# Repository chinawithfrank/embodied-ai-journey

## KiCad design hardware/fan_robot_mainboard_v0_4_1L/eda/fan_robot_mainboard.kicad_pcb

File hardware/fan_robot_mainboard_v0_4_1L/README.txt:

FanRobot V0.4 单面铜重设计试排 / 工程草案 / 禁止投板
打开 eda/fan_robot_mainboard.kicad_pro。本目录没有生产 ZIP。V0.3 制造文件没有改动。

目标：保留 60×50 mm 外形、54×44 mm 安装孔距、三节干电池、V0.3 网表与集成芯片。将贴片元件放在 F.Cu 侧，插针和 JST 插件从另一侧安装，正面焊接；保留禁布天线区域。重排了开关、阻容和测试点。原外壳的按键开窗、相机接线、底部插拔和电池线净空不能沿用未经核对的假设。J5 改面后应按新板针1核对线束，不能照旧板照片插接。

当前板：背面全板禁走线、禁铺铜、禁过孔。KiCad 工作叠层仍显示 F/B，通孔器件仍使用通孔焊盘模型；不能用默认双层导出命令投板。ESP32 中心 41 号接地焊盘保留，取消了原封装用来连到底层的散热孔，这项改变并未经过热验证。新板未达到制造条件；原理图 ERC 无误不等于 PCB 全部连通。

检查依据：checks/drc.rpt 为完整原生 DRC（含与原理图的一致性）；checks/status.json 为本版几何/开路统计。评审时以这两个文件为准。
继续设计：按功能分区重新排列相机并口、USB差分对、电源输入到两路开关转换器、电机驱动到限流电阻；逐项处理跨线。若采用0Ω跨接，需进入原理图、BOM与贴装文件；高电流与反馈不能随意通过细跳线绕行。若放大板框，需同步核对机壳。投板前必须清除未连接/短路、检查实际单铜面焊盘及钻孔、复核地回路和散热，并用新板生成专属 Gerber/BOM/CPL。不要从 V0.3 删掉底铜来下单。

工程维护：layout.py 用 KiCad 10 Python 从邻目录 V0.3 重新生成布局（会覆盖 PCB），可带临时 DSN 输出路径；使用 Freerouting 2.1.0 做禁止背面和过孔的试布；finish.py 输入选定的 SES，导入并重新填铜。用 kicad-cli pcb drc --all-track-errors --schematic-parity 输出最新报告，再运行 check-layout.py。在打开现成草案时不需要运行这些脚本。

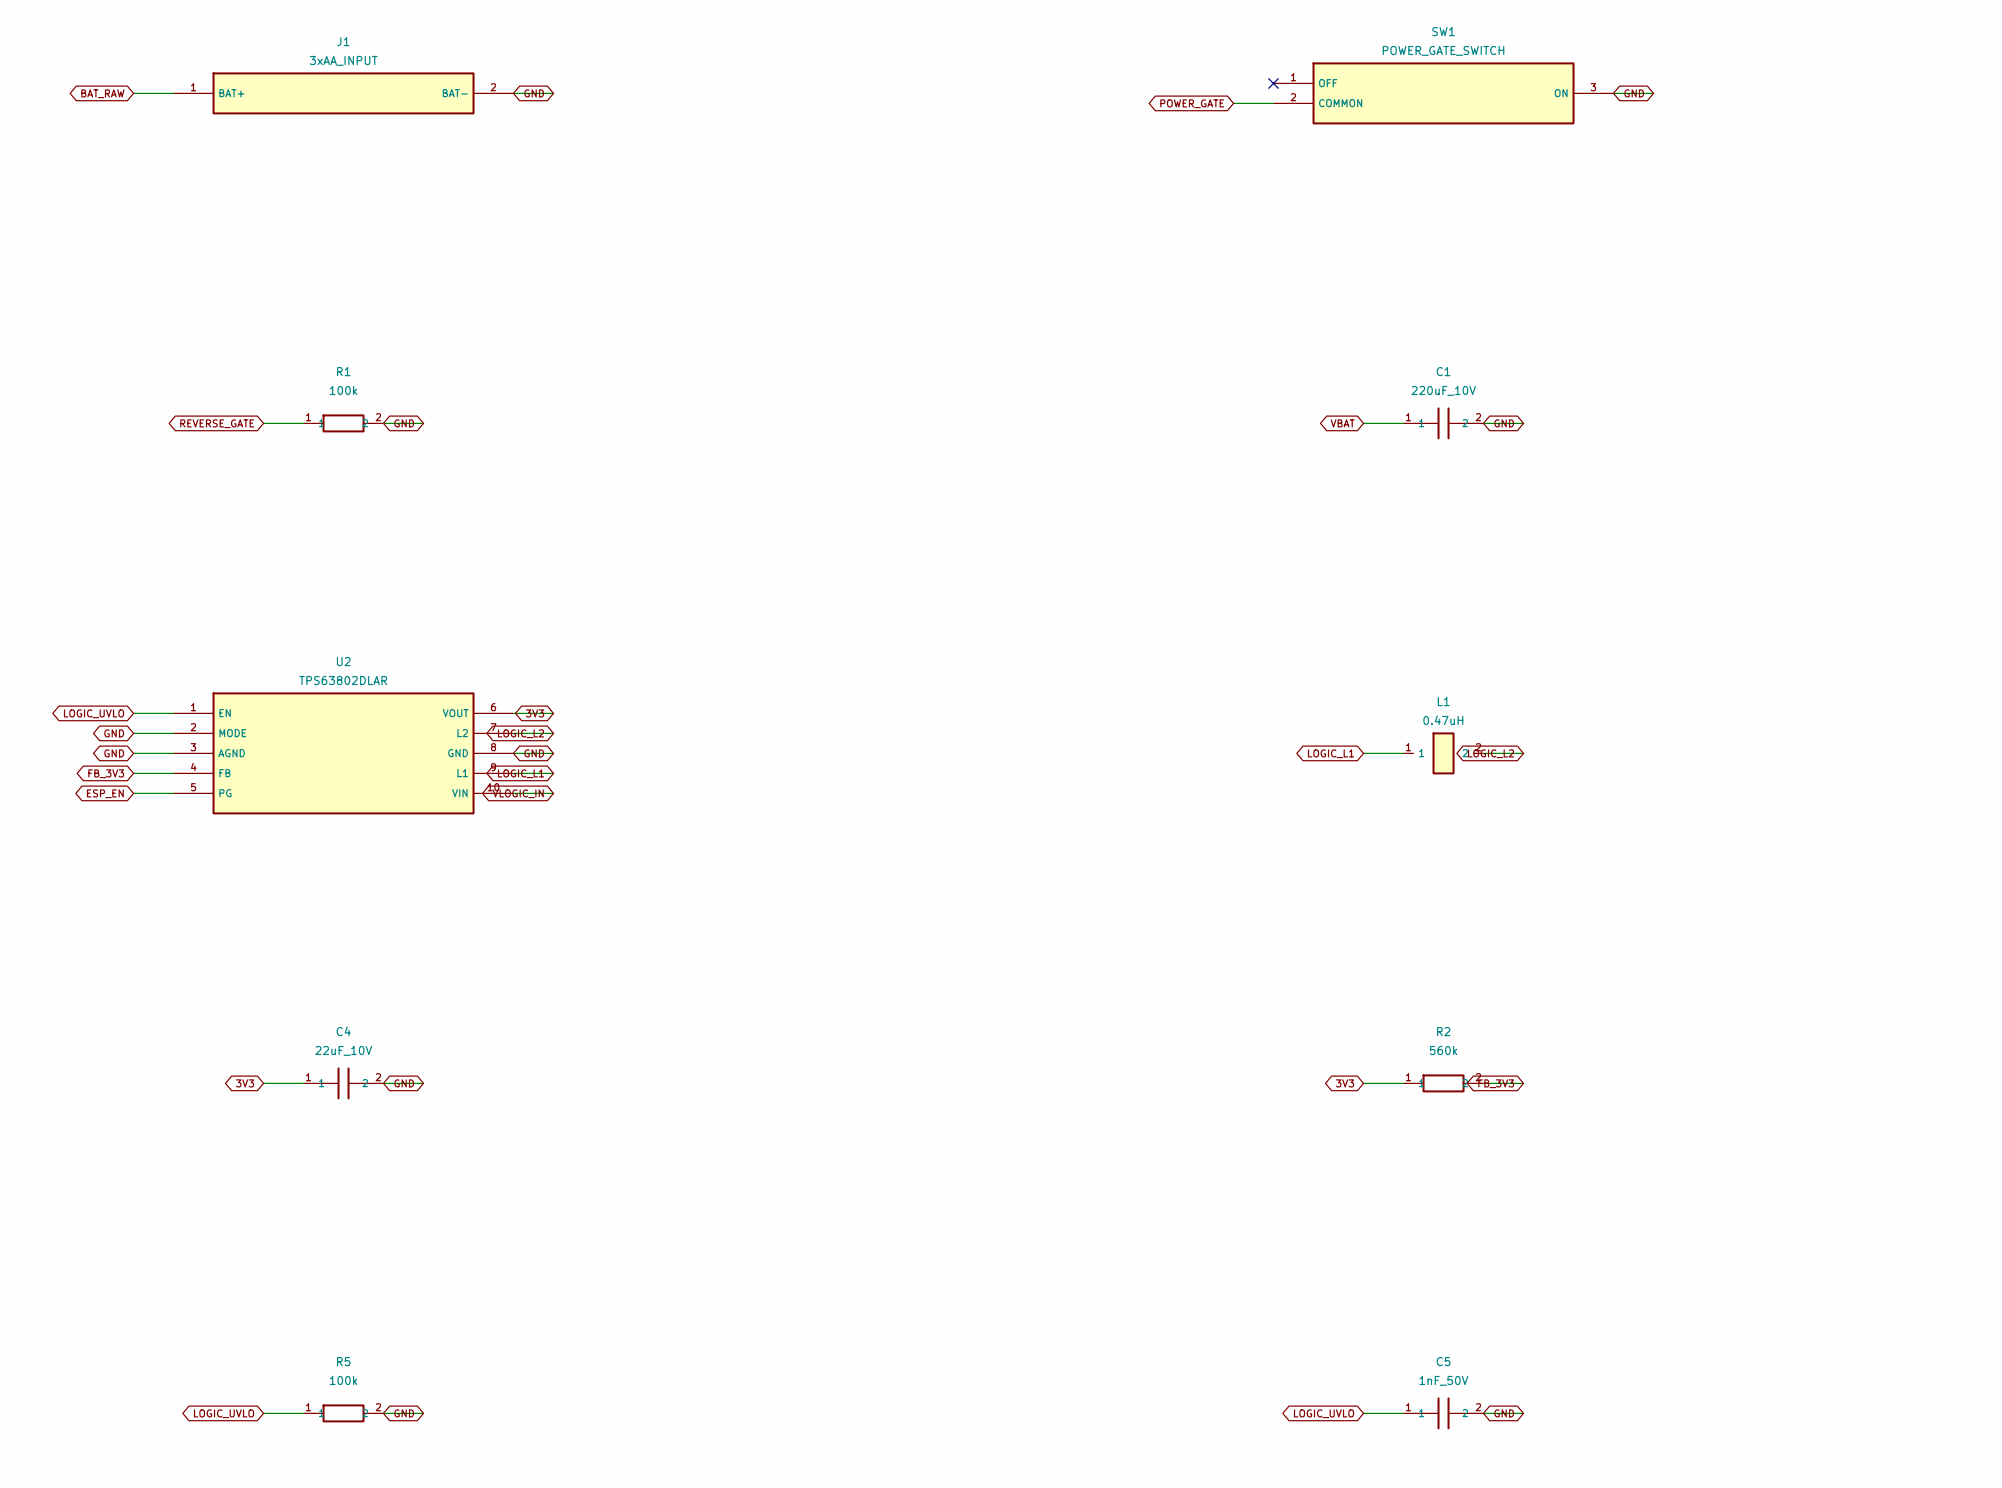
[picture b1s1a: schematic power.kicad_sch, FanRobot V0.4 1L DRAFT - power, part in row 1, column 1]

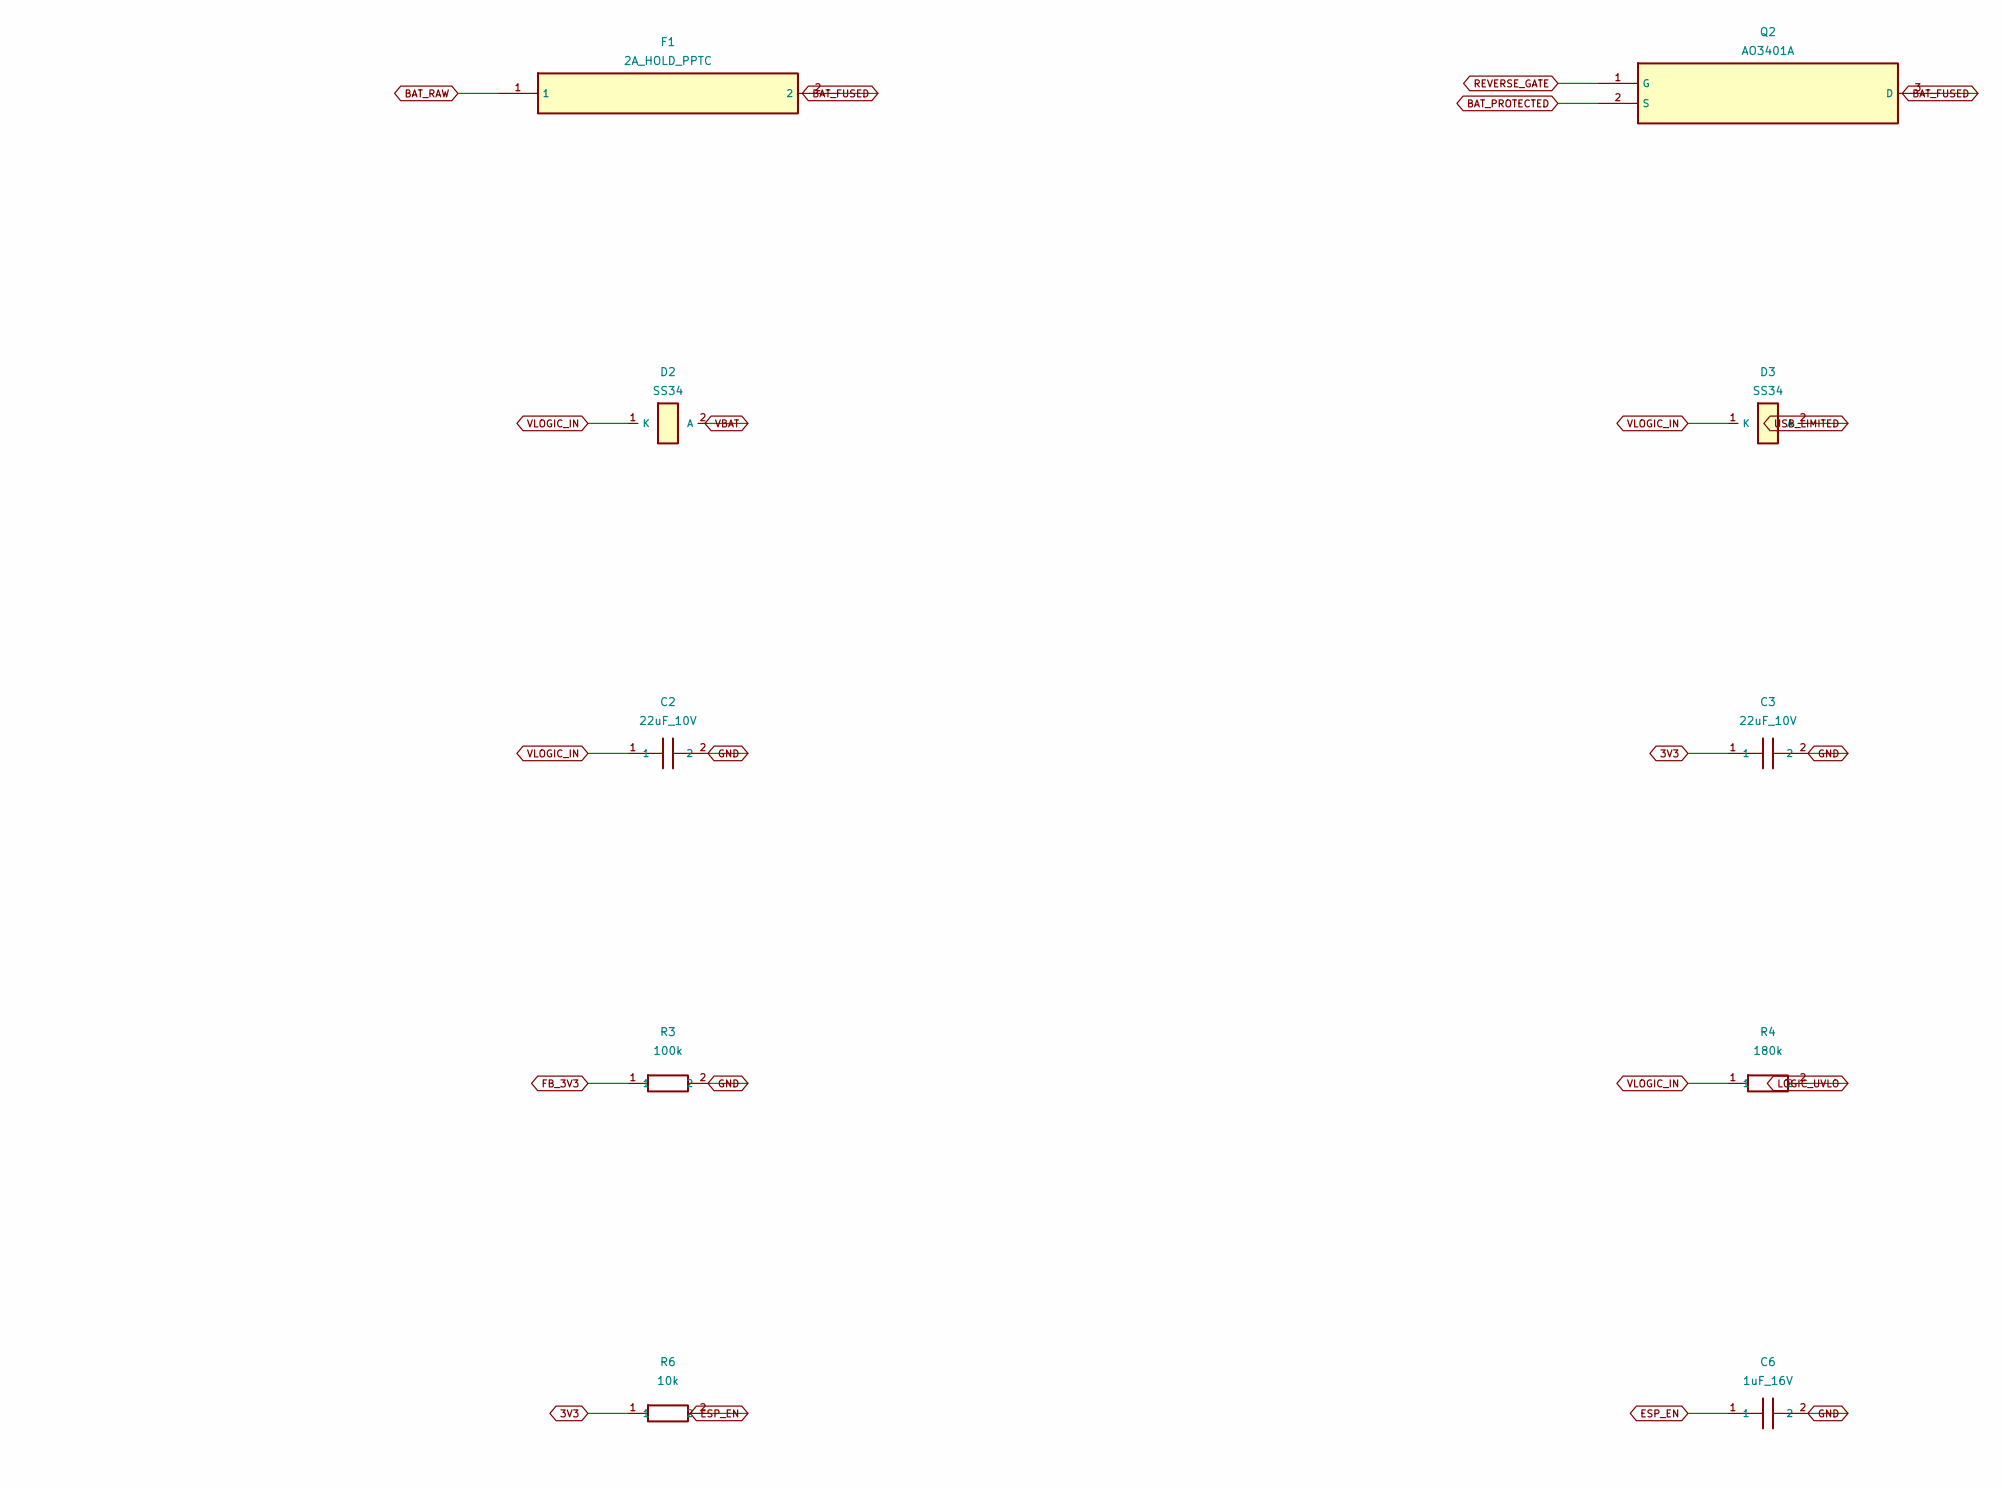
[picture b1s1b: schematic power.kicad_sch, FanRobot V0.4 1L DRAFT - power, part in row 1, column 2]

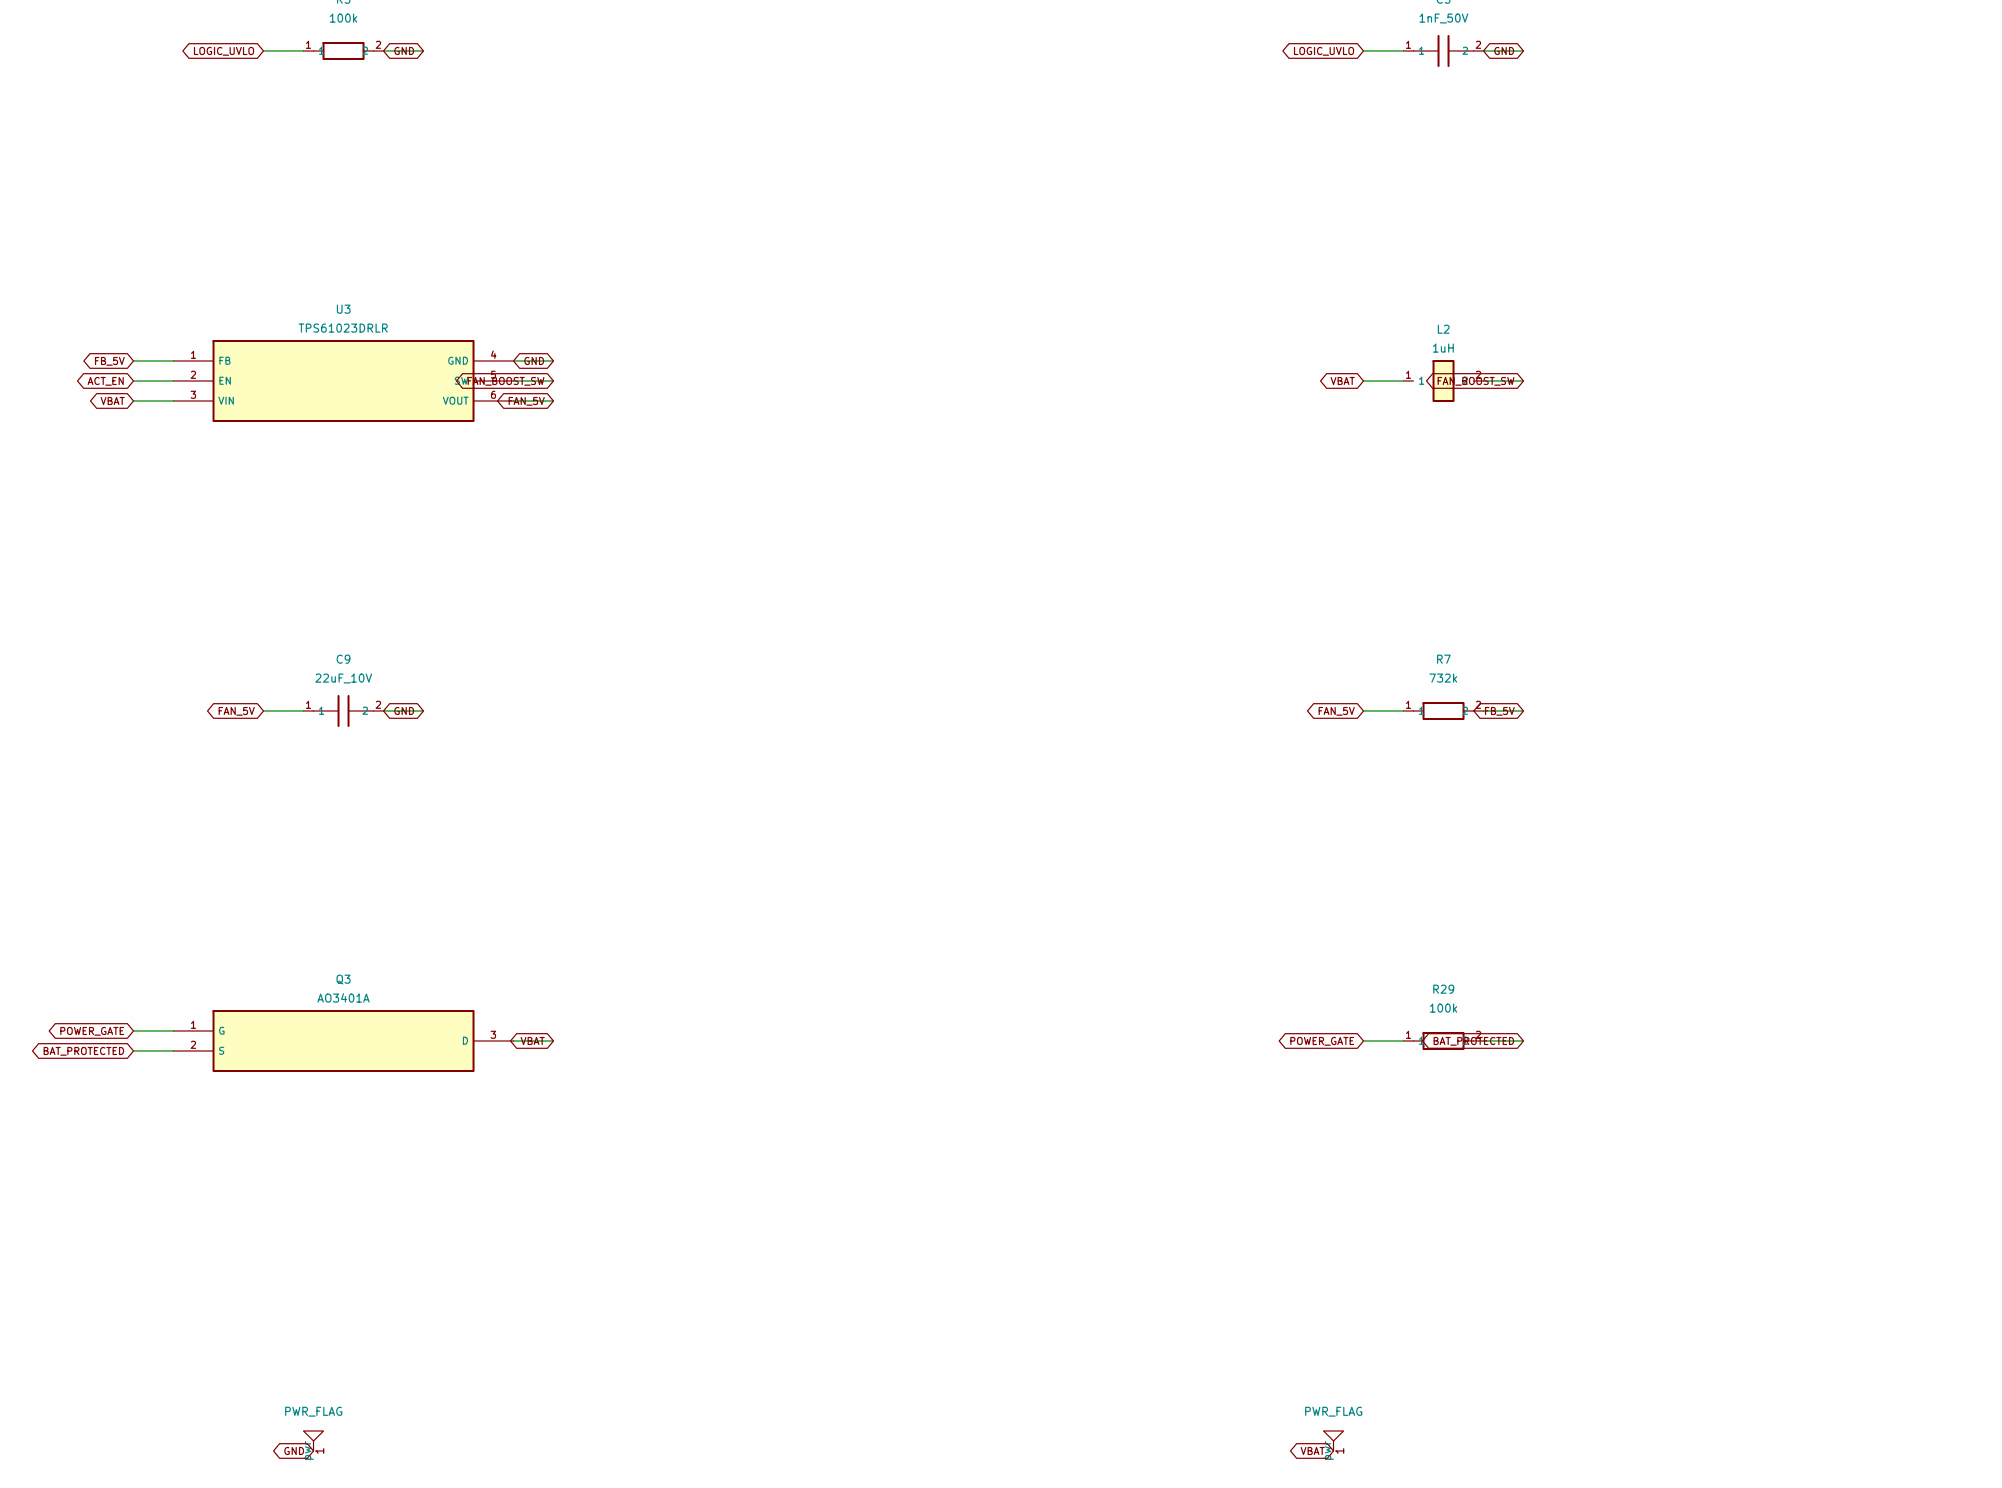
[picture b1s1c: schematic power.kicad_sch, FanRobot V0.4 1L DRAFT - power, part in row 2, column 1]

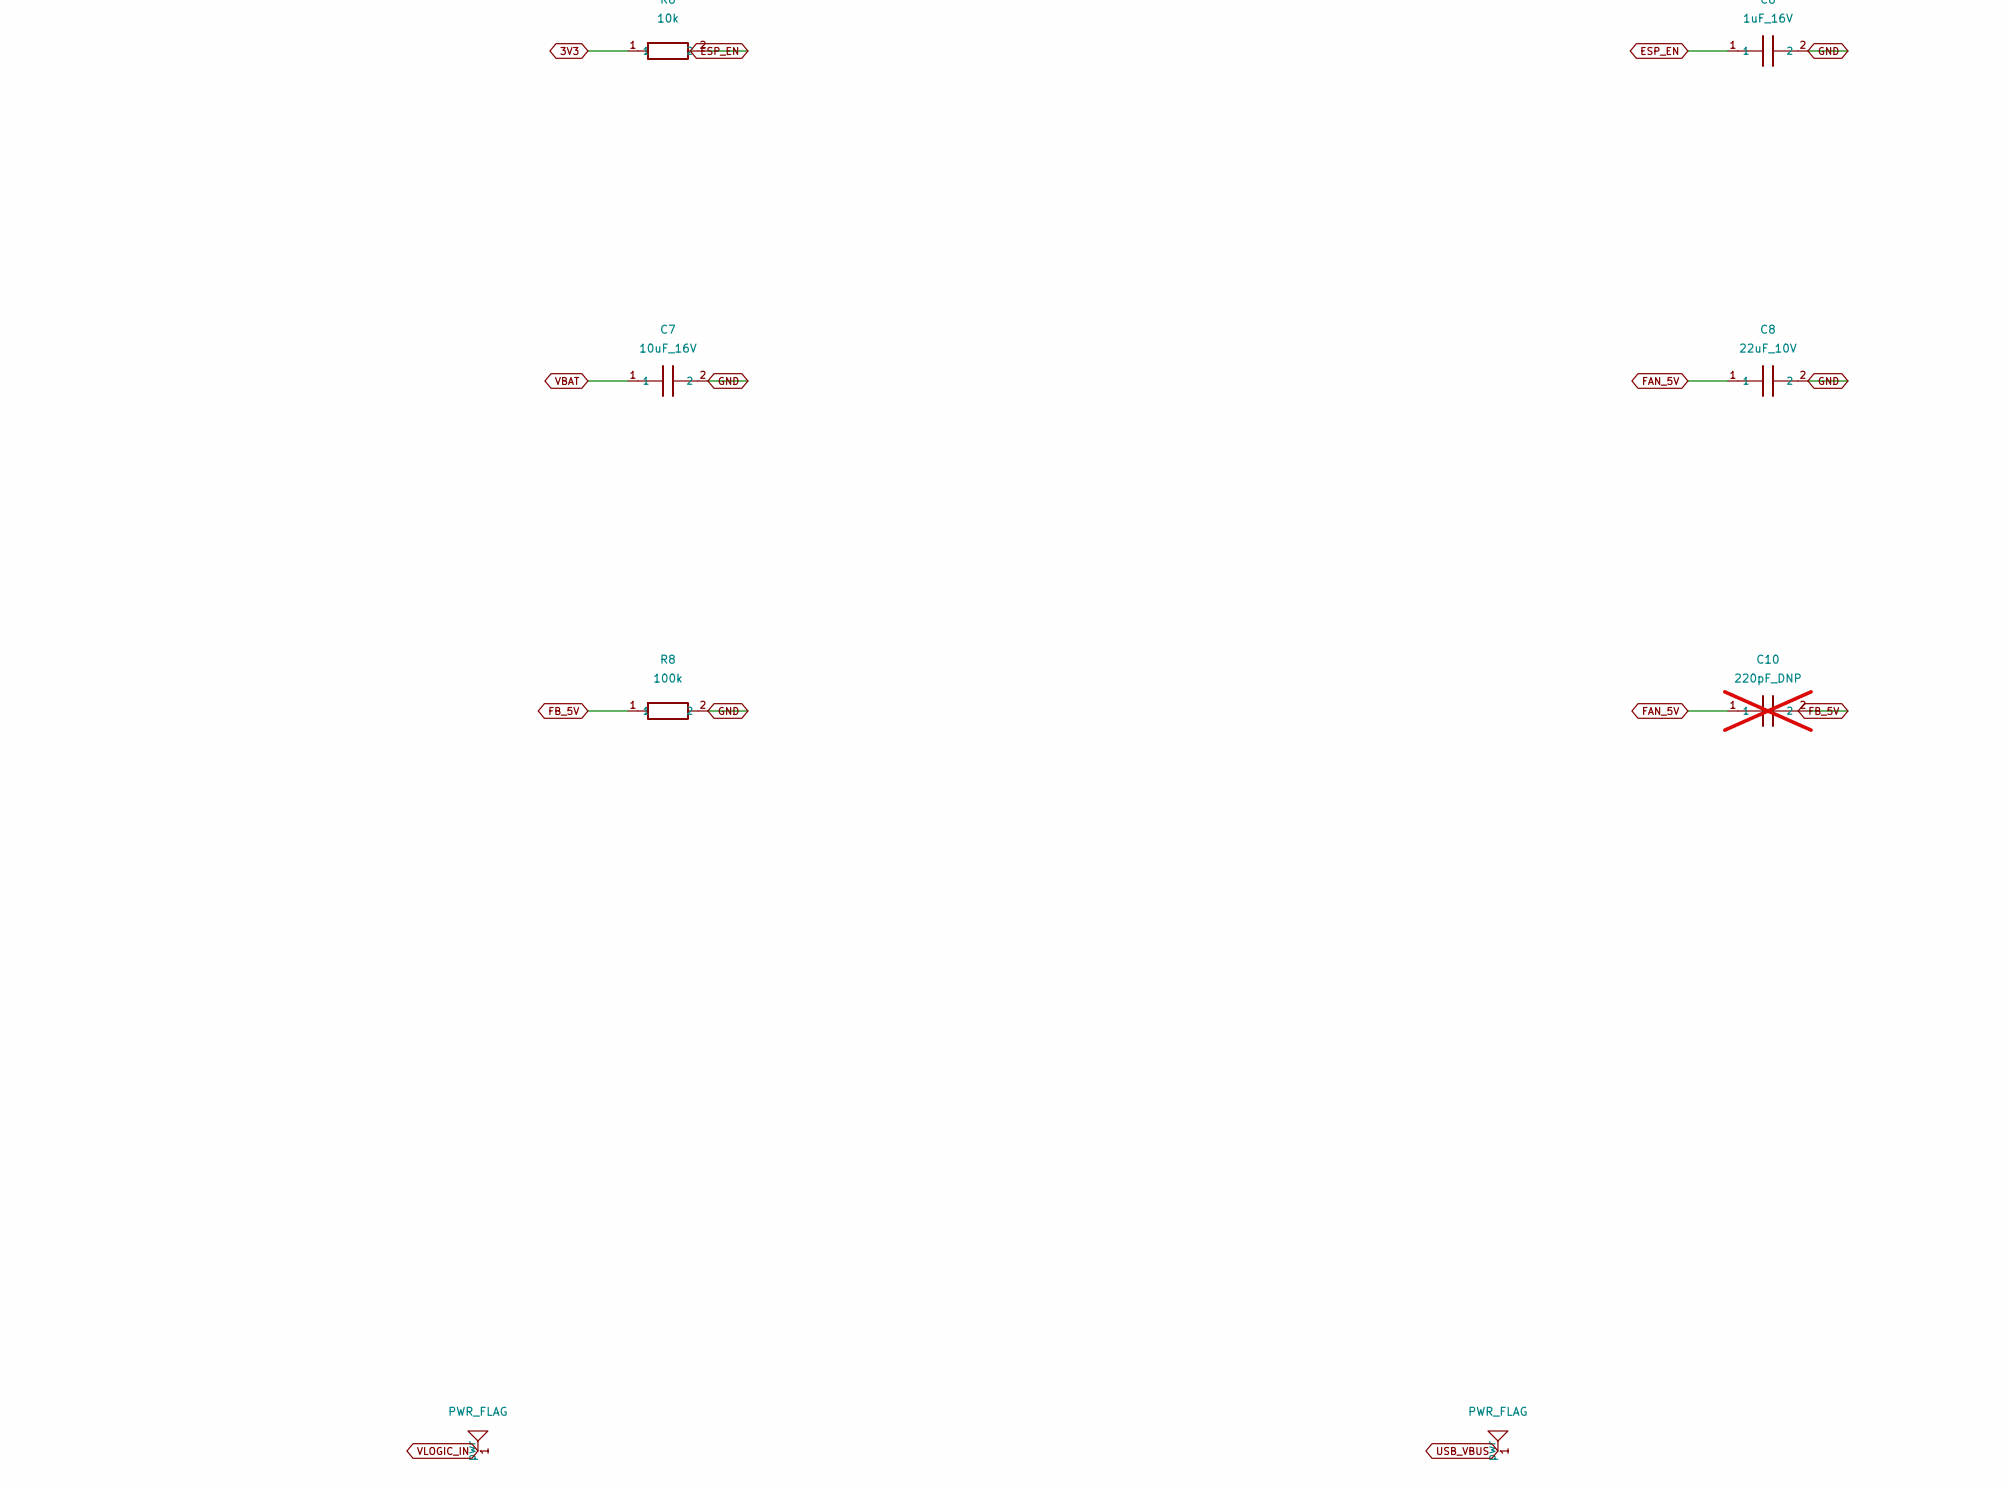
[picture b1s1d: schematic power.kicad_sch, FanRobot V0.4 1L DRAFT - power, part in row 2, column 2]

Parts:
C1: 220uF_10V; CP_OSCON_C6_6.3x5.9; MPN 10SVPE220M; LCSC C165949
C2, C3, C4, C8, C9: 22uF_10V; C_0805_2012Metric; MPN GRM21BR61A226ME51L; LCSC C77074
C5: 1nF_50V; C_0603_1608Metric; MPN CL10B102KB8NNNC; LCSC C1588
C6: 1uF_16V; C_0805_2012Metric; MPN GRM21BR71C105KA01L; LCSC C77079
C7: 10uF_16V; C_0805_2012Metric; MPN GRM21BR61C106KE15L; LCSC C77075
C10: 220pF_DNP; C_0603_1608Metric; MPN CL10C221JB8NNNC; LCSC C27675; not fitted
D2, D3: SS34; D_SMA; MPN SS34; LCSC C8678
F1: 2A_HOLD_PPTC; Fuse_1812_4532Metric; MPN MF-MSMF200-2; LCSC C210837
J1: 3xAA_INPUT; JST_XH_B2B-XH-A_1x02_P2.50mm_Vertical; MPN B2B-XH-A(LF)(SN); LCSC C158012
L1: 0.47uH; L_Murata_DFE201612E; MPN DFE201612E-R47M=P2; LCSC C668312
L2: 1uH; L_Wuerth_MAPI-4030; MPN 74438357010; LCSC C5542269
Q2, Q3: AO3401A; SOT-23; MPN AO3401A; LCSC C15127
R1, R3, R5, R8, R29: 100k; R_0603_1608Metric; MPN 0603WAF1003T5E; LCSC C25803
R2: 560k; R_0603_1608Metric; MPN 0603WAF5603T5E; LCSC C23203
R4: 180k; R_0603_1608Metric; MPN 0603WAF1803T5E; LCSC C22827
R6: 10k; R_0603_1608Metric; MPN 0603WAF1002T5E; LCSC C25804
R7: 732k; R_0603_1608Metric; MPN 0603WAF7323T5E; LCSC C23239
SW1: POWER_GATE_SWITCH; SW_SPDT_CK_JS102011SAQN; MPN JS102011SAQN; LCSC C221660
U2: TPS63802DLAR; TPS63802_DLA0010A; MPN TPS63802DLAR; LCSC C2845237
U3: TPS61023DRLR; SOT-563; MPN TPS61023DRLR; LCSC C919459

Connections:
3V3: C3.1, C4.1, R2.1, R6.1, U2.6 (VOUT); also elsewhere on the board
ACT_EN: U3.2 (EN); also elsewhere on the board
BAT_FUSED: F1.2, Q2.3 (D)
BAT_PROTECTED: Q2.2 (S), Q3.2 (S), R29.2
BAT_RAW: F1.1, J1.1 (BAT+)
ESP_EN: C6.1, R6.2, U2.5 (PG); also elsewhere on the board
FAN_5V: C8.1, C9.1, C10.1, R7.1, U3.6 (VOUT); also elsewhere on the board
FAN_BOOST_SW: L2.2, U3.5 (SW)
FB_3V3: R2.2, R3.1, U2.4 (FB)
FB_5V: C10.2, R7.2, R8.1, U3.1 (FB)
GND: C1.2, C2.2, C3.2, C4.2, C5.2, C6.2, C7.2, C8.2, C9.2, J1.2 (BAT-), R1.2, R3.2, R5.2, R8.2, SW1.3 (ON), U2.2 (MODE), U2.3 (AGND), U2.8 (GND), U3.4 (GND); also elsewhere on the board
LOGIC_L1: L1.1, U2.9 (L1)
LOGIC_L2: L1.2, U2.7 (L2)
LOGIC_UVLO: C5.1, R4.2, R5.1, U2.1 (EN)
POWER_GATE: Q3.1 (G), R29.1, SW1.2 (COMMON)
REVERSE_GATE: Q2.1 (G), R1.1
USB_LIMITED: D3.2 (A); also elsewhere on the board
VBAT: C1.1, C7.1, D2.2 (A), L2.1, Q3.3 (D), U3.3 (VIN); also elsewhere on the board
VLOGIC_IN: C2.1, D2.1 (K), D3.1 (K), R4.1, U2.10 (VIN)

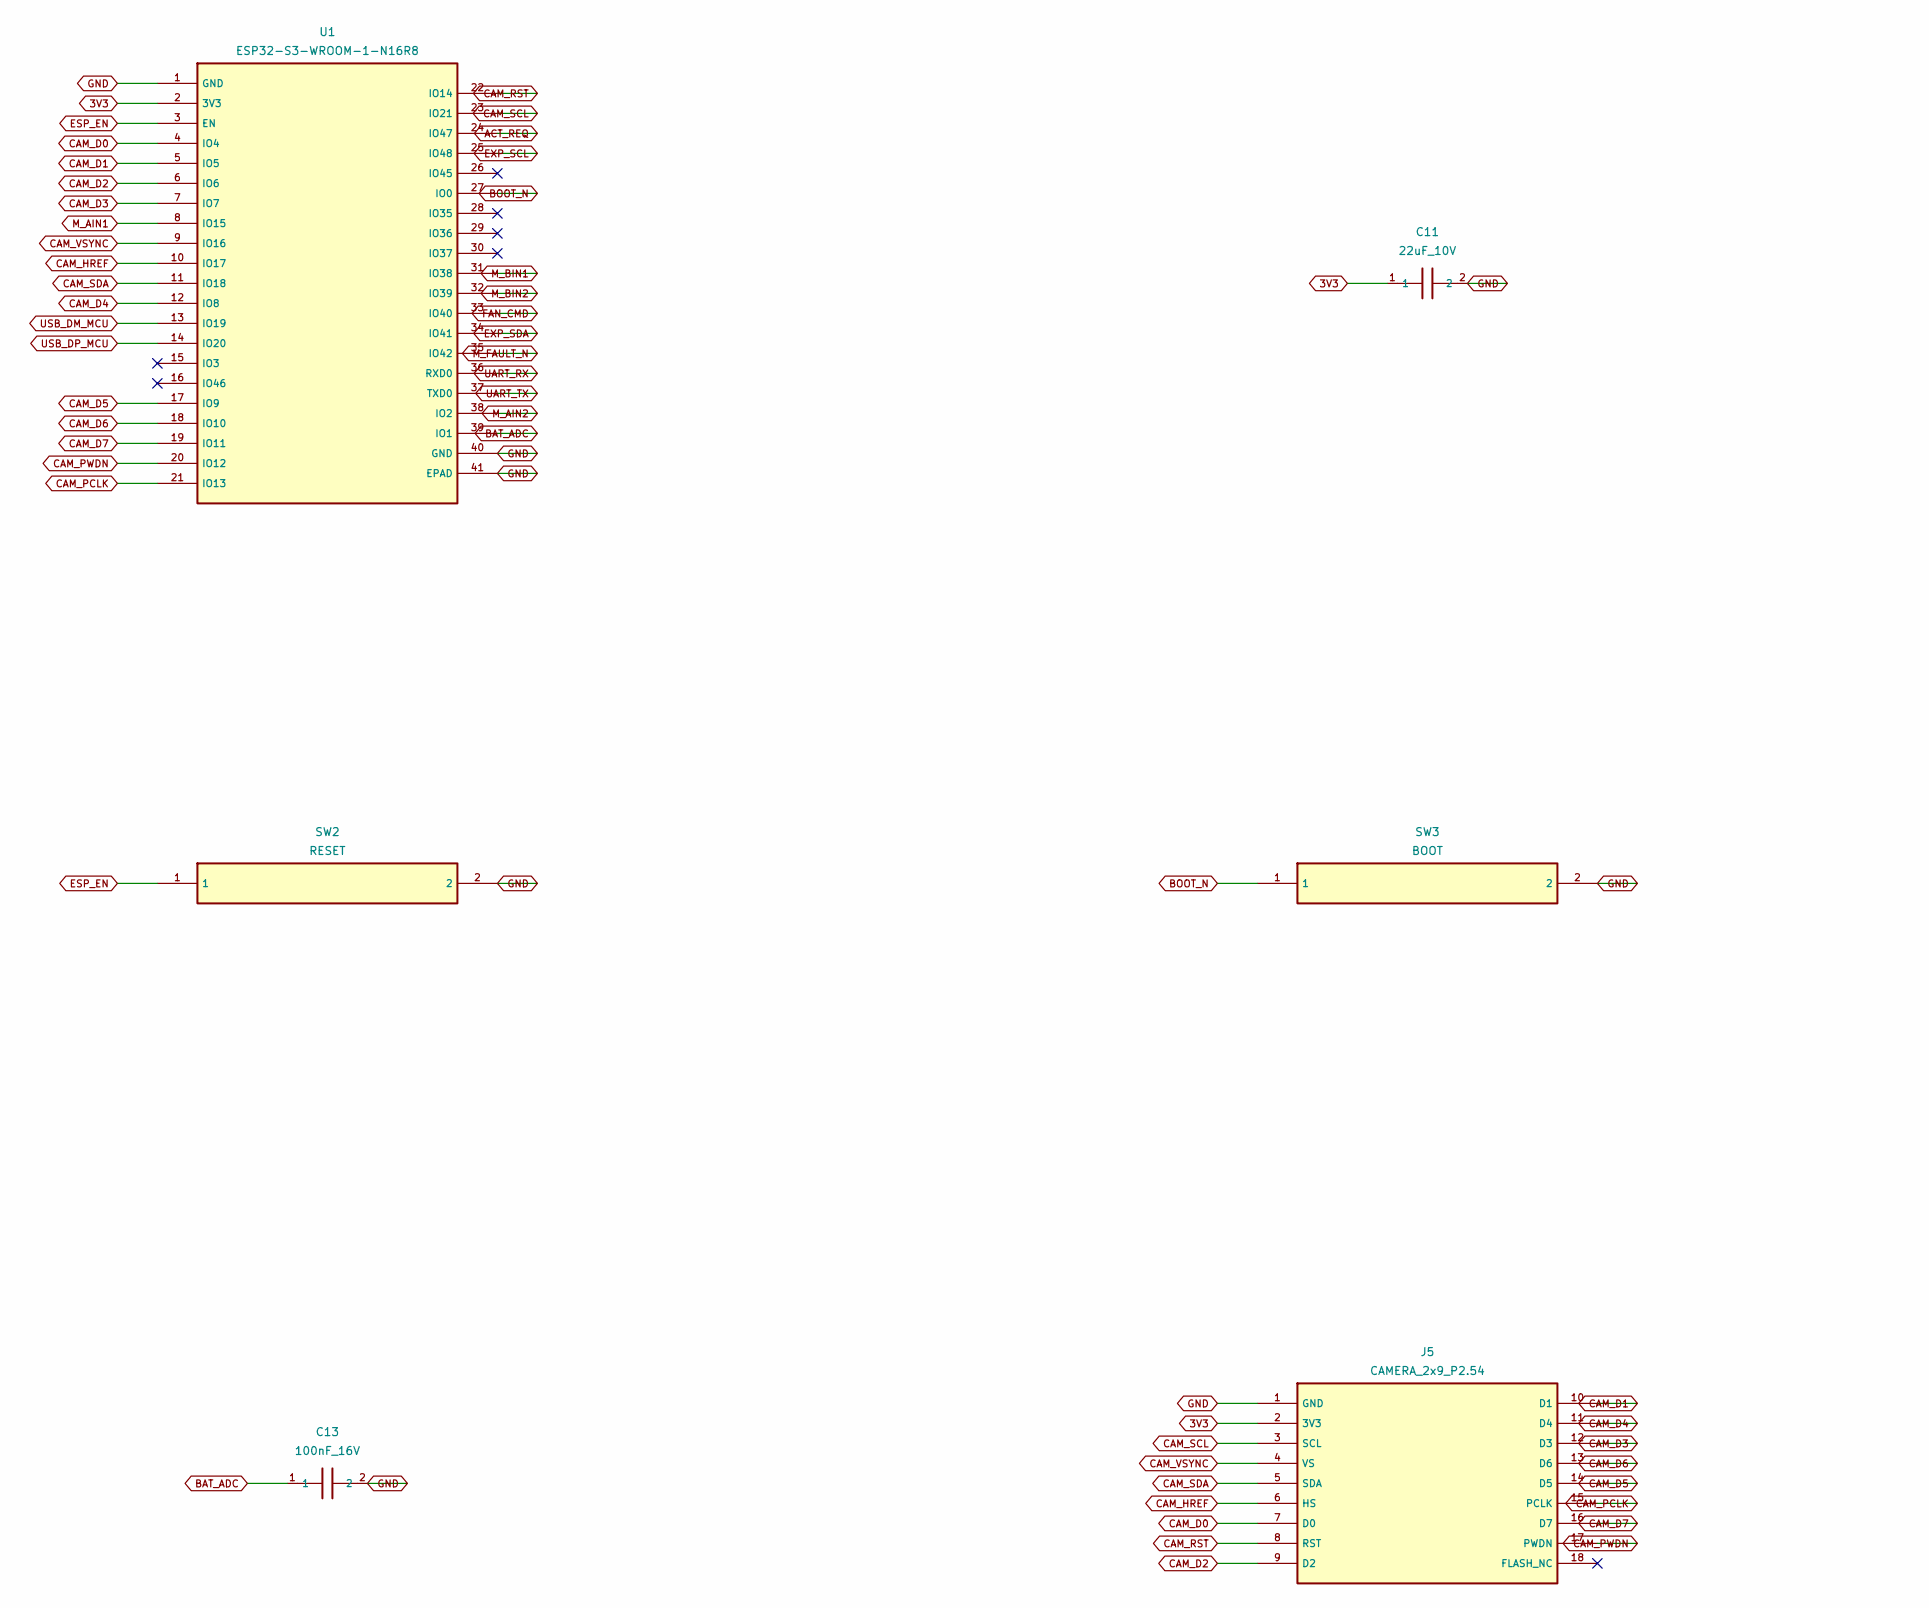
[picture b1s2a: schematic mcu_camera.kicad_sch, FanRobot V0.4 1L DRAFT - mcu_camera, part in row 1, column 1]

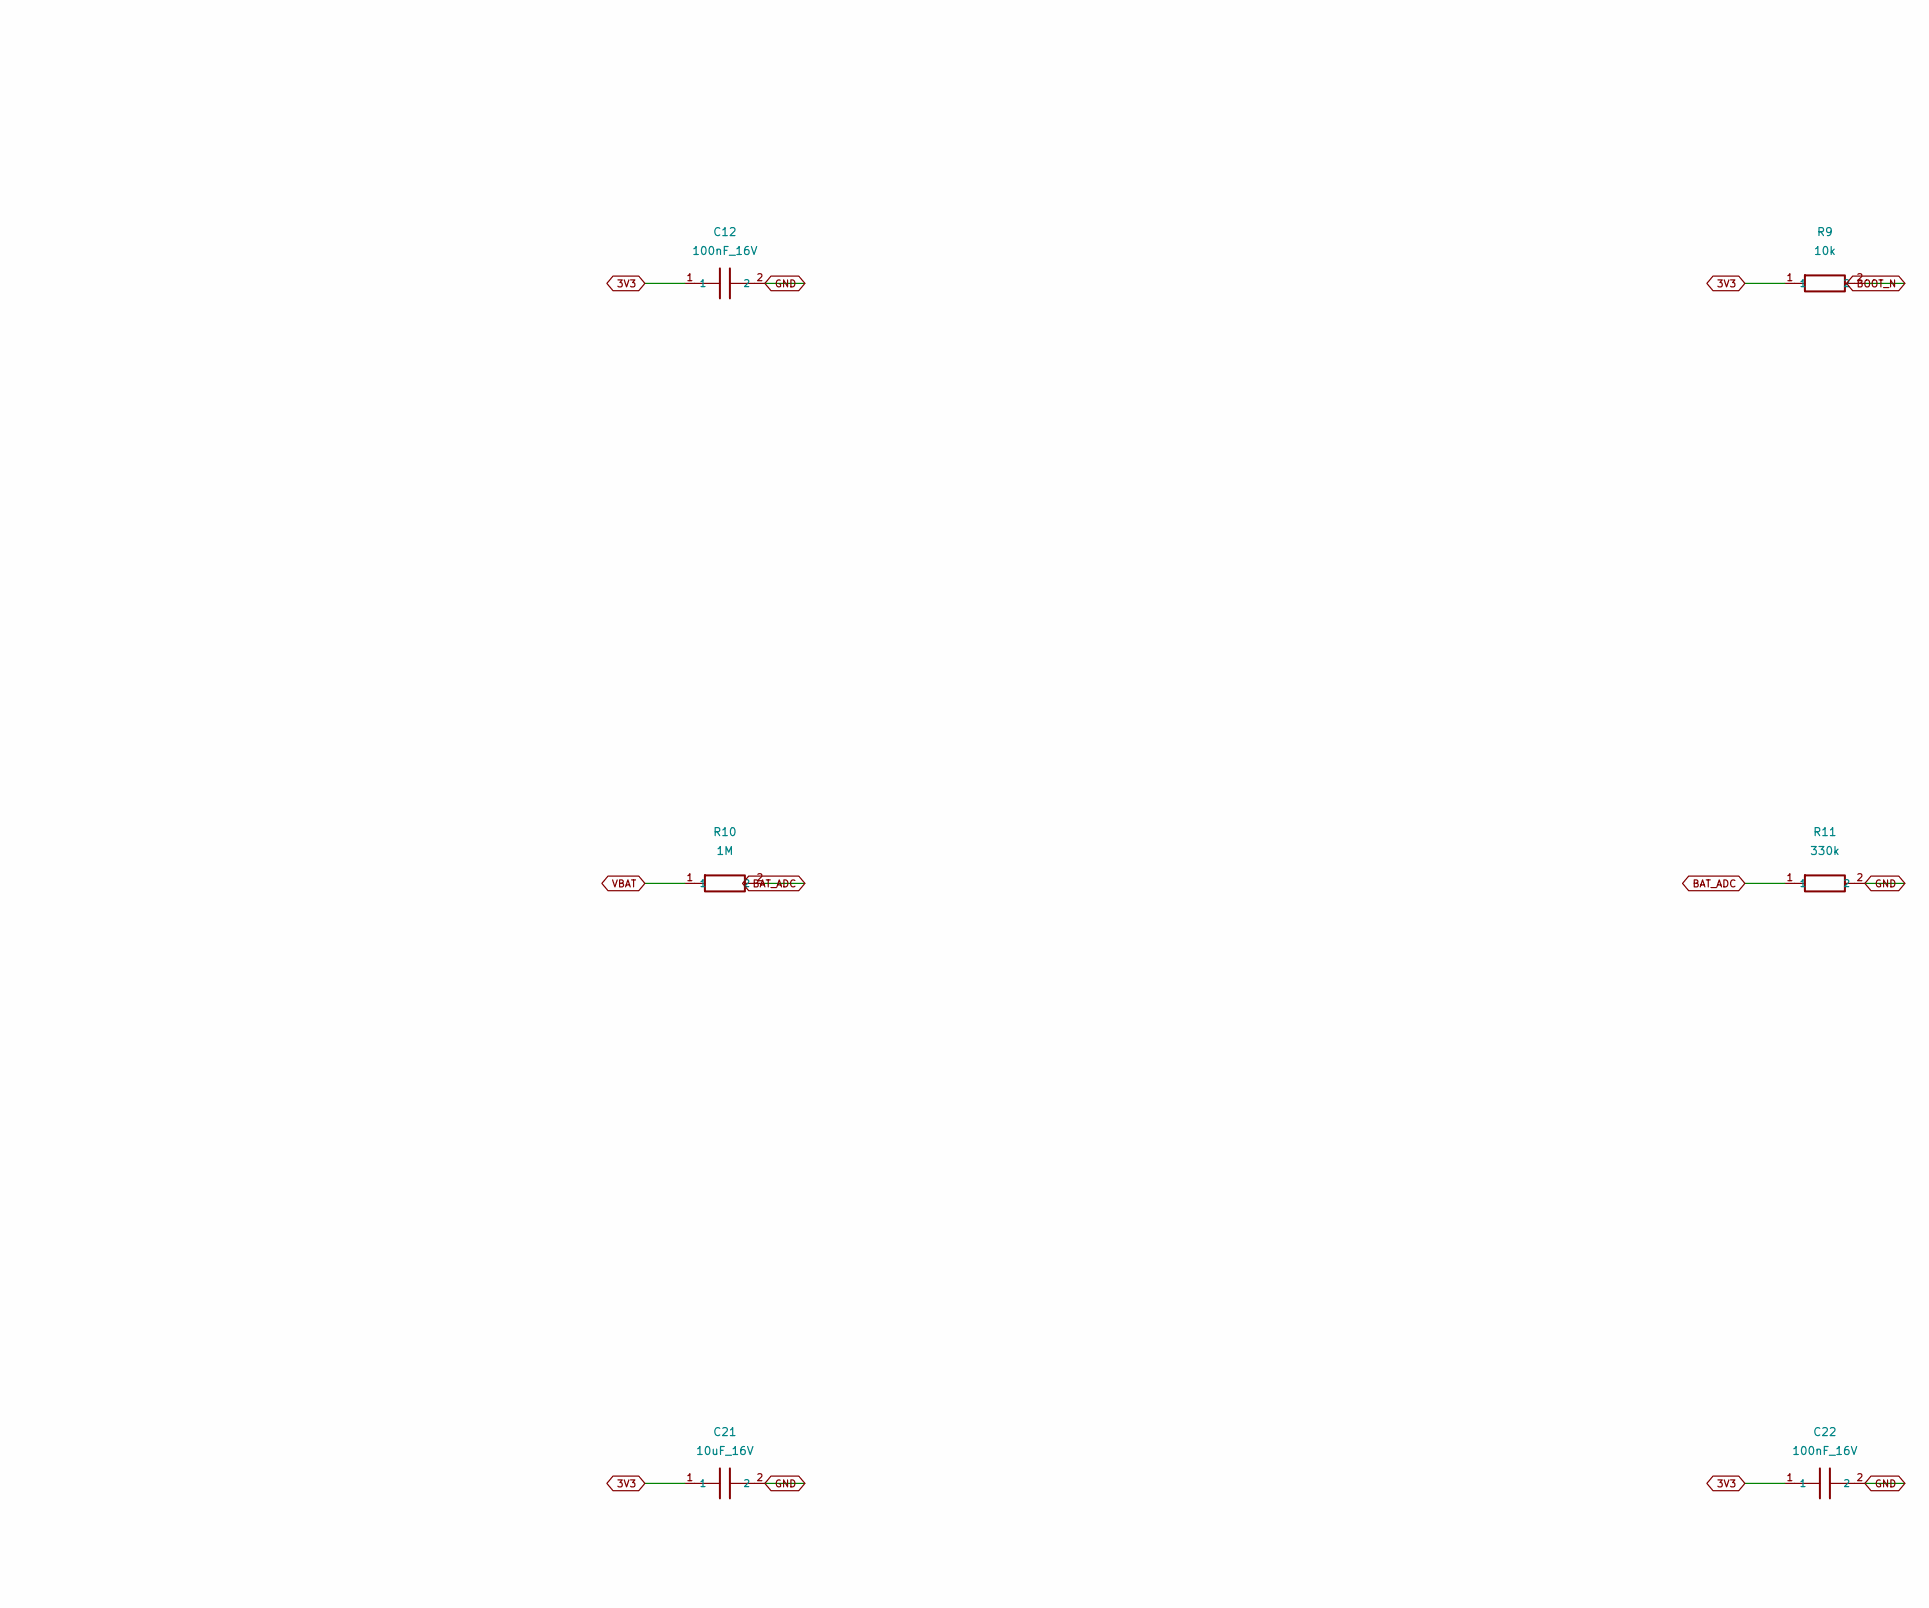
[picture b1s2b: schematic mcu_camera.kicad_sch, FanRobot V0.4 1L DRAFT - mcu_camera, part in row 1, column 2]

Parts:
C11: 22uF_10V; C_0805_2012Metric; MPN GRM21BR61A226ME51L; LCSC C77074
C12, C13, C22: 100nF_16V; C_0603_1608Metric; MPN GRM188R71C104KA01D; LCSC C45000
C21: 10uF_16V; C_0805_2012Metric; MPN GRM21BR61C106KE15L; LCSC C77075
J5: CAMERA_2x9_P2.54; PinSocket_2x09_P2.54mm_Vertical; MPN 2.54-2*9P; LCSC C71956
R9: 10k; R_0603_1608Metric; MPN 0603WAF1002T5E; LCSC C25804
R10: 1M; R_0603_1608Metric; MPN 0603WAF1004T5E; LCSC C22935
R11: 330k; R_0603_1608Metric; MPN 0603WAF3303T5E; LCSC C23137
SW2: RESET; SW_Push_1P1T_NO_CK_KMR2; MPN KMR221GLFS; LCSC C72443
SW3: BOOT; SW_Push_1P1T_NO_CK_KMR2; MPN KMR221GLFS; LCSC C72443
U1: ESP32-S3-WROOM-1-N16R8; ESP32-S3-WROOM-1; MPN ESP32-S3-WROOM-1-N16R8; LCSC C2913202

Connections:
3V3: C11.1, C12.1, C21.1, C22.1, J5.2 (3V3), R9.1, U1.2 (3V3); also elsewhere on the board
ACT_REQ: U1.24 (IO47); also elsewhere on the board
BAT_ADC: C13.1, R10.2, R11.1, U1.39 (IO1); also elsewhere on the board
BOOT_N: R9.2, SW3.1, U1.27 (IO0); also elsewhere on the board
CAM_D0: J5.7 (D0), U1.4 (IO4)
CAM_D1: J5.10 (D1), U1.5 (IO5)
CAM_D2: J5.9 (D2), U1.6 (IO6)
CAM_D3: J5.12 (D3), U1.7 (IO7)
CAM_D4: J5.11 (D4), U1.12 (IO8)
CAM_D5: J5.14 (D5), U1.17 (IO9)
CAM_D6: J5.13 (D6), U1.18 (IO10)
CAM_D7: J5.16 (D7), U1.19 (IO11)
CAM_HREF: J5.6 (HS), U1.10 (IO17)
CAM_PCLK: J5.15 (PCLK), U1.21 (IO13)
CAM_PWDN: J5.17 (PWDN), U1.20 (IO12)
CAM_RST: J5.8 (RST), U1.22 (IO14)
CAM_SCL: J5.3 (SCL), U1.23 (IO21)
CAM_SDA: J5.5 (SDA), U1.11 (IO18)
CAM_VSYNC: J5.4 (VS), U1.9 (IO16)
ESP_EN: SW2.1, U1.3 (EN); also elsewhere on the board
EXP_SCL: U1.25 (IO48); also elsewhere on the board
EXP_SDA: U1.34 (IO41); also elsewhere on the board
FAN_CMD: U1.33 (IO40); also elsewhere on the board
GND: C11.2, C12.2, C13.2, C21.2, C22.2, J5.1 (GND), R11.2, SW2.2, SW3.2, U1.1 (GND), U1.40 (GND), U1.41 (EPAD); also elsewhere on the board
M_AIN1: U1.8 (IO15); also elsewhere on the board
M_AIN2: U1.38 (IO2); also elsewhere on the board
M_BIN1: U1.31 (IO38); also elsewhere on the board
M_BIN2: U1.32 (IO39); also elsewhere on the board
M_FAULT_N: U1.35 (IO42); also elsewhere on the board
UART_RX: U1.36 (RXD0); also elsewhere on the board
UART_TX: U1.37 (TXD0); also elsewhere on the board
USB_DM_MCU: U1.13 (IO19); also elsewhere on the board
USB_DP_MCU: U1.14 (IO20); also elsewhere on the board
VBAT: R10.1; also elsewhere on the board
